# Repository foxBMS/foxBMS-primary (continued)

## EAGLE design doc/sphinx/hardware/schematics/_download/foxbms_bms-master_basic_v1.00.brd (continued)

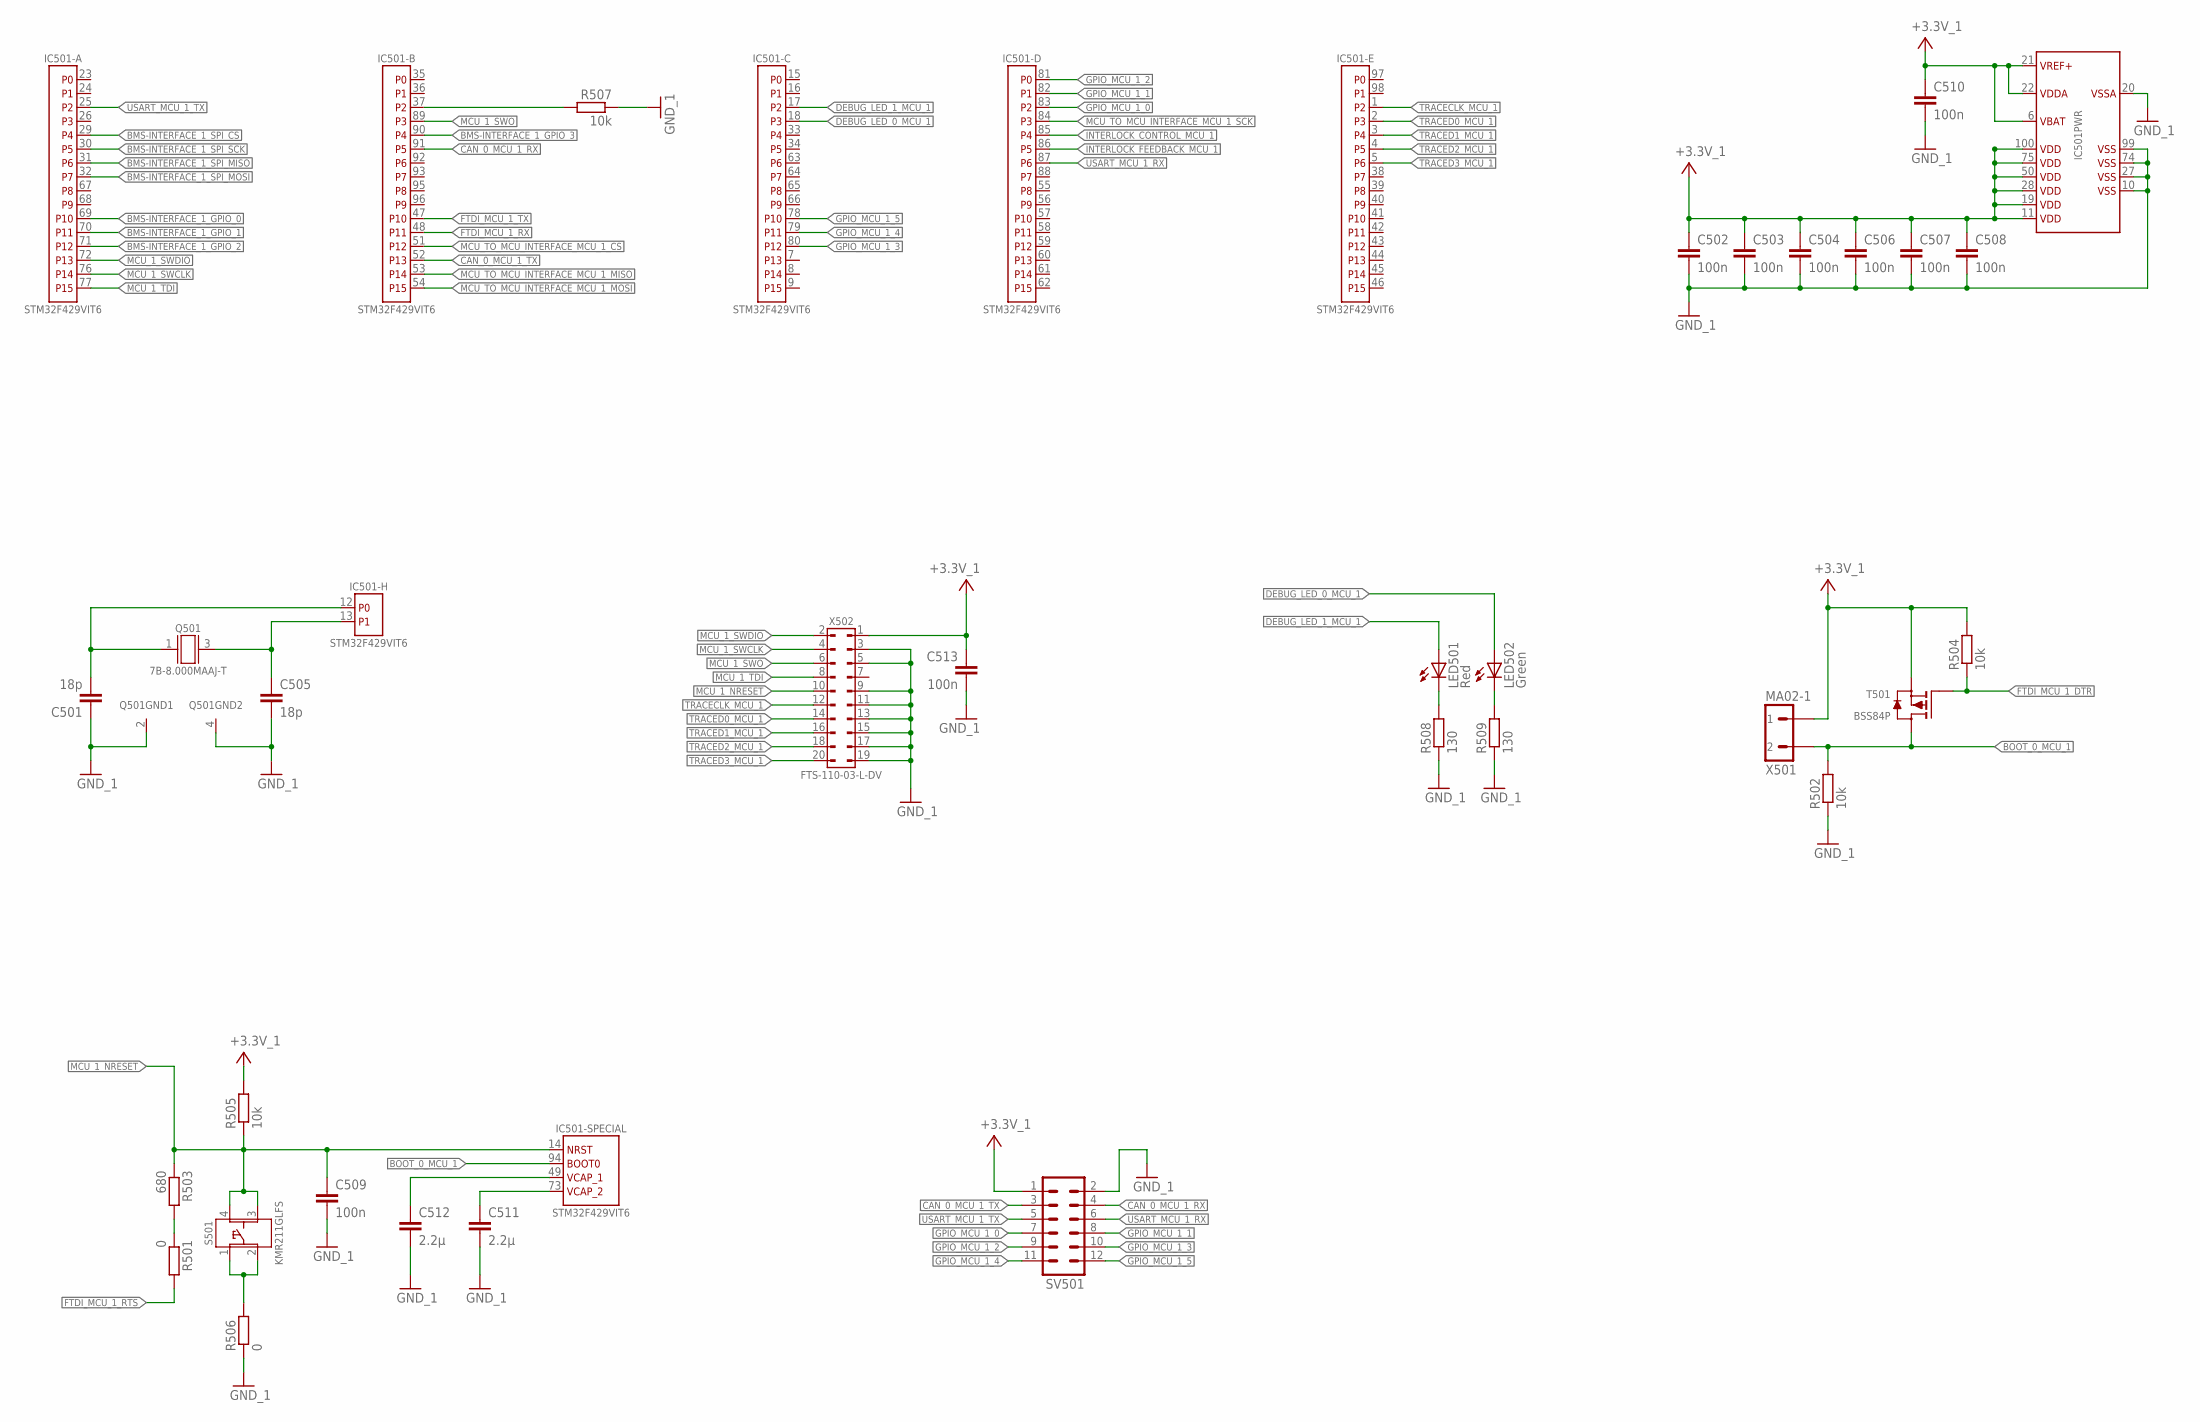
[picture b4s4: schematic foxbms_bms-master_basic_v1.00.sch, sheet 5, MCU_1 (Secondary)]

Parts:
C501, C505: 18p; C0603
C502, C503, C504, C506, C507, C508, C509, C510, C513: 100n; C0603
C511, C512: 2.2µ; C0603
IC501: STM32F429VIT6; IC_SMD_LQFP100_R_ST_REV01
LED501: Red; CHIP-LED0603
LED502: Green; CHIP-LED0603
Q501: 7B-8.000MAAJ-T; G_SMD_5,00MM_X_3,20MM_0,90MM_(7B)_TXC_REV01
R501, R506: 0; R0603
R502, R504, R505, R507: 10k; R0603
R503: 680; R0603
R508, R509: 130; R0603
S501: KMR211GLFS; S_SMD_4,60MMX2,80MMX1,90MM_R_CK-COMPONENTS_REV01
SV501: MA06-2
T501: BSS84P; V_SMD_SOT23_(TO-236AB)_R_INFINEON_REV01
X501: MA02-1
X502: SAMTEC_FTS_20POL_HEADER_VERTIKAL_REV01; X_SMD_FTS_110-03_(20POL)_R_SAMTEC_REV01

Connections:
+3.3V_1: C502.1, C503.1, C504.1, C506.1, C507.1, C508.1, C510.1, C513.1, IC501.6 (VBAT), IC501.11 (VDD1), IC501.19 (VDD2), IC501.21 (VREF+), IC501.22 (VDDA), IC501.28 (VDD3), IC501.50 (VDD4), IC501.75 (VDD5), IC501.100 (VDD6), R504.2, R505.2, SV501.1, T501.2 (S), X501.1, X502.1; also elsewhere on the board
BMS-INTERFACE_1_GPIO_0: IC501.69 (P10); also elsewhere on the board
BMS-INTERFACE_1_GPIO_1: IC501.70 (P11); also elsewhere on the board
BMS-INTERFACE_1_GPIO_2: IC501.71 (P12); also elsewhere on the board
BMS-INTERFACE_1_GPIO_3: IC501.90 (P4); also elsewhere on the board
BMS-INTERFACE_1_SPI_CS: IC501.29 (P4); also elsewhere on the board
BMS-INTERFACE_1_SPI_MISO: IC501.31 (P6); also elsewhere on the board
BMS-INTERFACE_1_SPI_MOSI: IC501.32 (P7); also elsewhere on the board
BMS-INTERFACE_1_SPI_SCK: IC501.30 (P5); also elsewhere on the board
BOOT_0_MCU_1: IC501.94 (BOOT0), R502.2, T501.3 (D), X501.2
CAN_0_MCU_1_RX: IC501.91 (P5), SV501.4
CAN_0_MCU_1_TX: IC501.52 (P13), SV501.3
DEBUG_LED_0_MCU_1: IC501.18 (P3), LED502.A
DEBUG_LED_1_MCU_1: IC501.17 (P2), LED501.A
FTDI_MCU_1_DTR: R504.1, T501.1 (G); also elsewhere on the board
FTDI_MCU_1_RTS: R501.2; also elsewhere on the board
FTDI_MCU_1_RX: IC501.48 (P11); also elsewhere on the board
FTDI_MCU_1_TX: IC501.47 (P10); also elsewhere on the board
GND_1: C501.1, C502.2, C503.2, C504.2, C505.2, C506.2, C507.2, C508.2, C509.2, C510.2, C511.2, C512.2, C513.2, IC501.10 (VSS1), IC501.20 (VSSA), IC501.27 (VSS2), IC501.74 (VSS3), IC501.99 (VSS4), Q501.2 (GND), Q501.4 (GND), R502.1, R506.1, R507.1, R508.1, R509.1, SV501.2, X502.3, X502.5, X502.9, X502.11, X502.13, X502.15, X502.17, X502.19; also elsewhere on the board
GPIO_MCU_1_0: IC501.83 (P2), SV501.7
GPIO_MCU_1_1: IC501.82 (P1), SV501.8
GPIO_MCU_1_2: IC501.81 (P0), SV501.9
GPIO_MCU_1_3: IC501.80 (P12), SV501.10
GPIO_MCU_1_4: IC501.79 (P11), SV501.11
GPIO_MCU_1_5: IC501.78 (P10), SV501.12
INTERLOCK_CONTROL_MCU_1: IC501.85 (P4); also elsewhere on the board
INTERLOCK_FEEDBACK_MCU_1: IC501.86 (P5); also elsewhere on the board
MCU_1_NRESET: C509.1, IC501.14 (NRST), R503.1, R505.1, S501.3, S501.4, X502.10
MCU_1_SWCLK: IC501.76 (P14), X502.4
MCU_1_SWDIO: IC501.72 (P13), X502.2
MCU_1_SWO: IC501.89 (P3), X502.6
MCU_1_TDI: IC501.77 (P15), X502.8
MCU_TO_MCU_INTERFACE_MCU_1_CS: IC501.51 (P12); also elsewhere on the board
MCU_TO_MCU_INTERFACE_MCU_1_MISO: IC501.53 (P14); also elsewhere on the board
MCU_TO_MCU_INTERFACE_MCU_1_MOSI: IC501.54 (P15); also elsewhere on the board
MCU_TO_MCU_INTERFACE_MCU_1_SCK: IC501.84 (P3); also elsewhere on the board
unnamed: C501.2, IC501.12 (P0), Q501.1 (A)
unnamed: C505.1, IC501.13 (P1), Q501.3 (B)
unnamed: R506.2, S501.1, S501.2
unnamed: LED502.C, R509.2
unnamed: LED501.C, R508.2
unnamed: C511.1, IC501.73 (VCAP_2)
unnamed: C512.1, IC501.49 (VCAP_1)
unnamed: IC501.37 (P2), R507.2
unnamed: R501.1, R503.2
TRACECLK_MCU_1: IC501.1 (P2), X502.12
TRACED0_MCU_1: IC501.2 (P3), X502.14
TRACED1_MCU_1: IC501.3 (P4), X502.16
TRACED2_MCU_1: IC501.4 (P5), X502.18
TRACED3_MCU_1: IC501.5 (P6), X502.20
USART_MCU_1_RX: IC501.87 (P6), SV501.6
USART_MCU_1_TX: IC501.25 (P2), SV501.5

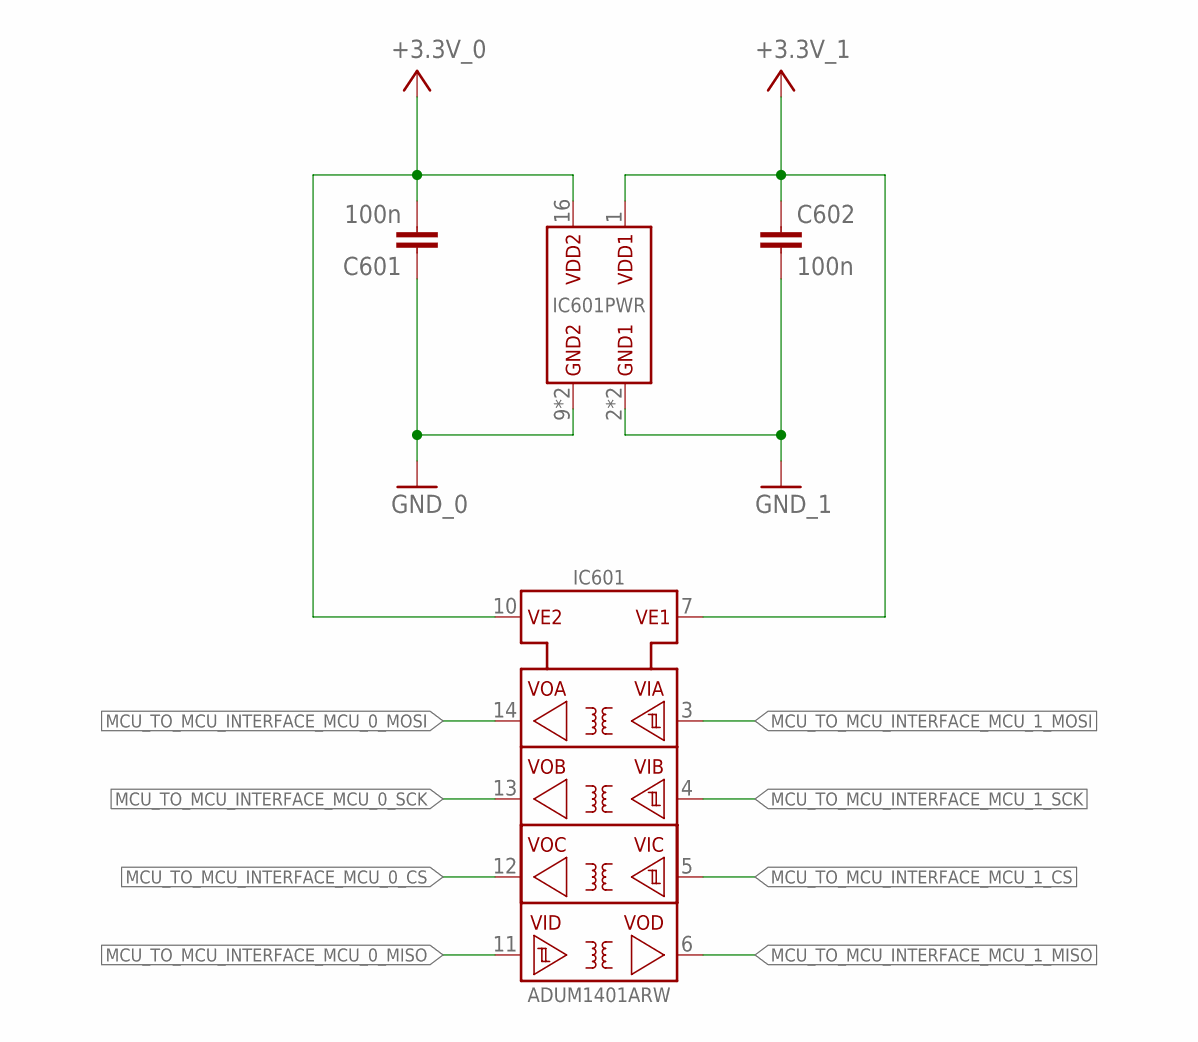
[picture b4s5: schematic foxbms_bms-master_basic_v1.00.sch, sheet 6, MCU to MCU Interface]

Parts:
C601, C602: 100n; C0603
IC601: ADUM1401ARW; IC_SMD_SOIC-16_(JEDEC_MS-013-AA)_R_ANALOG_REV01

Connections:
+3.3V_0: C601.2, IC601.10 (VE2), IC601.16 (VDD2); also elsewhere on the board
+3.3V_1: C602.1, IC601.1 (VDD1), IC601.7 (VE1); also elsewhere on the board
GND_0: C601.1, IC601.9 (GND2), IC601.15 (GND2); also elsewhere on the board
GND_1: C602.2, IC601.2 (GND1), IC601.8 (GND1); also elsewhere on the board
MCU_TO_MCU_INTERFACE_MCU_0_CS: IC601.12 (VOC); also elsewhere on the board
MCU_TO_MCU_INTERFACE_MCU_0_MISO: IC601.11 (VID); also elsewhere on the board
MCU_TO_MCU_INTERFACE_MCU_0_MOSI: IC601.14 (VOA); also elsewhere on the board
MCU_TO_MCU_INTERFACE_MCU_0_SCK: IC601.13 (VOB); also elsewhere on the board
MCU_TO_MCU_INTERFACE_MCU_1_CS: IC601.5 (VIC); also elsewhere on the board
MCU_TO_MCU_INTERFACE_MCU_1_MISO: IC601.6 (VOD); also elsewhere on the board
MCU_TO_MCU_INTERFACE_MCU_1_MOSI: IC601.3 (VIA); also elsewhere on the board
MCU_TO_MCU_INTERFACE_MCU_1_SCK: IC601.4 (VIB); also elsewhere on the board

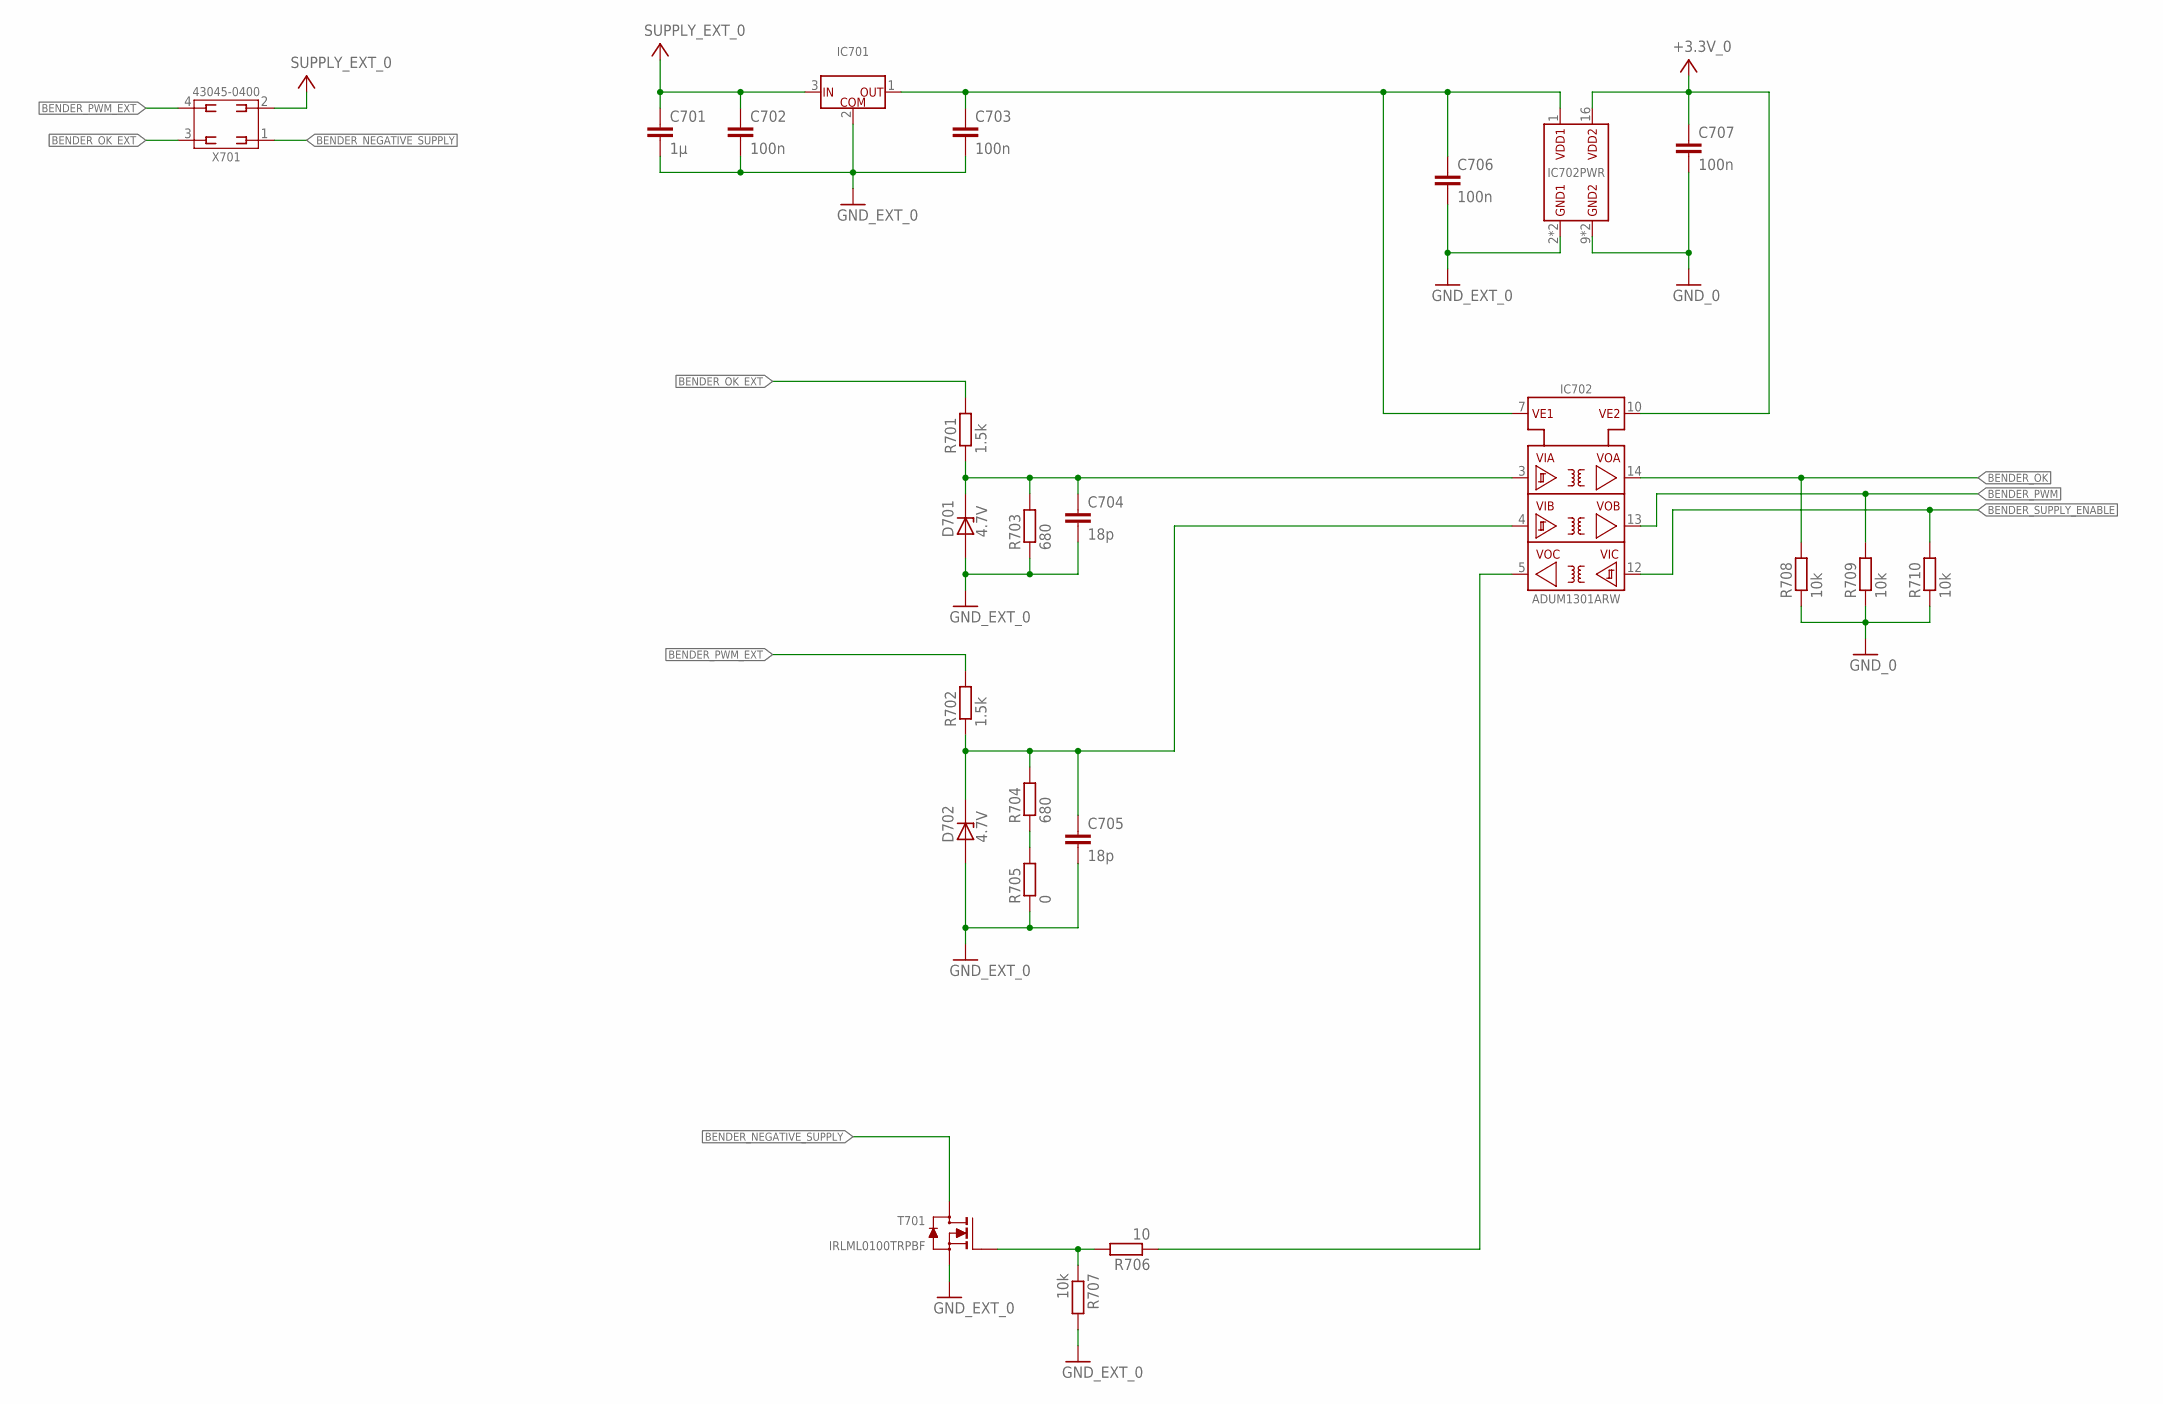
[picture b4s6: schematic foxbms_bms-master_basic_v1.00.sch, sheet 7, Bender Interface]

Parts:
C701: 1µ; C0603
C702, C703, C706, C707: 100n; C0603
C704, C705: 18p; C0603
D701, D702: 4.7V; SOD323
IC701: UA78L05ACPK; IC_SMD_SOT-89_(SC-62/TO-243)_(R-PSSO-F3)_R_TI_REV01
IC702: ADUM1301ARW; IC_SMD_SOIC-16_(JEDEC_MS-013-AA)_R_ANALOG_REV01
R701, R702: 1.5k; R0603
R703, R704: 680; R0603
R705: 0; R0603
R706: 10; R0603
R707, R708, R709, R710: 10k; R0603
T701: IRLML0100TRPBF; V_SMD_SOT-23_(TO-236AB)_R_IR_REV01
X701: 43045-0400_MOLEX_4PIN; X_TH_MOLEX_43045-0400_R_REV01

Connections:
+3.3V_0: C707.1, IC702.10 (VE2), IC702.16 (VDD2); also elsewhere on the board
BENDER_ADUM_SUPPLY: C703.1, C706.1, IC701.1 (OUT), IC702.1 (VDD1), IC702.7 (VE1)
BENDER_NEGATIVE_SUPPLY: T701.3 (D), X701.1
BENDER_OK: IC702.14 (VOA), R708.2; also elsewhere on the board
BENDER_OK_EXT: R701.2, X701.3
BENDER_PWM: IC702.13 (VOB), R709.2; also elsewhere on the board
BENDER_PWM_EXT: R702.2, X701.4
BENDER_SUPPLY_ENABLE: IC702.12 (VIC), R710.2; also elsewhere on the board
GND_0: C707.2, IC702.9 (GND2), IC702.15 (GND2), R708.1, R709.1, R710.1; also elsewhere on the board
GND_EXT_0: C701.2, C702.2, C703.2, C704.2, C705.2, C706.2, D701.A, D702.A, IC701.2 (COM), IC702.2 (GND1), IC702.8 (GND1), R703.1, R705.1, R707.2, T701.2 (S); also elsewhere on the board
unnamed: IC702.5 (VOC), R706.1
unnamed: R706.2, R707.1, T701.1 (G)
unnamed: C705.1, D702.C (K), IC702.4 (VIB), R702.1, R704.2
unnamed: C704.1, D701.C (K), IC702.3 (VIA), R701.1, R703.2
unnamed: R704.1, R705.2
SUPPLY_EXT_0: C701.1, C702.1, IC701.3 (IN), X701.2; also elsewhere on the board

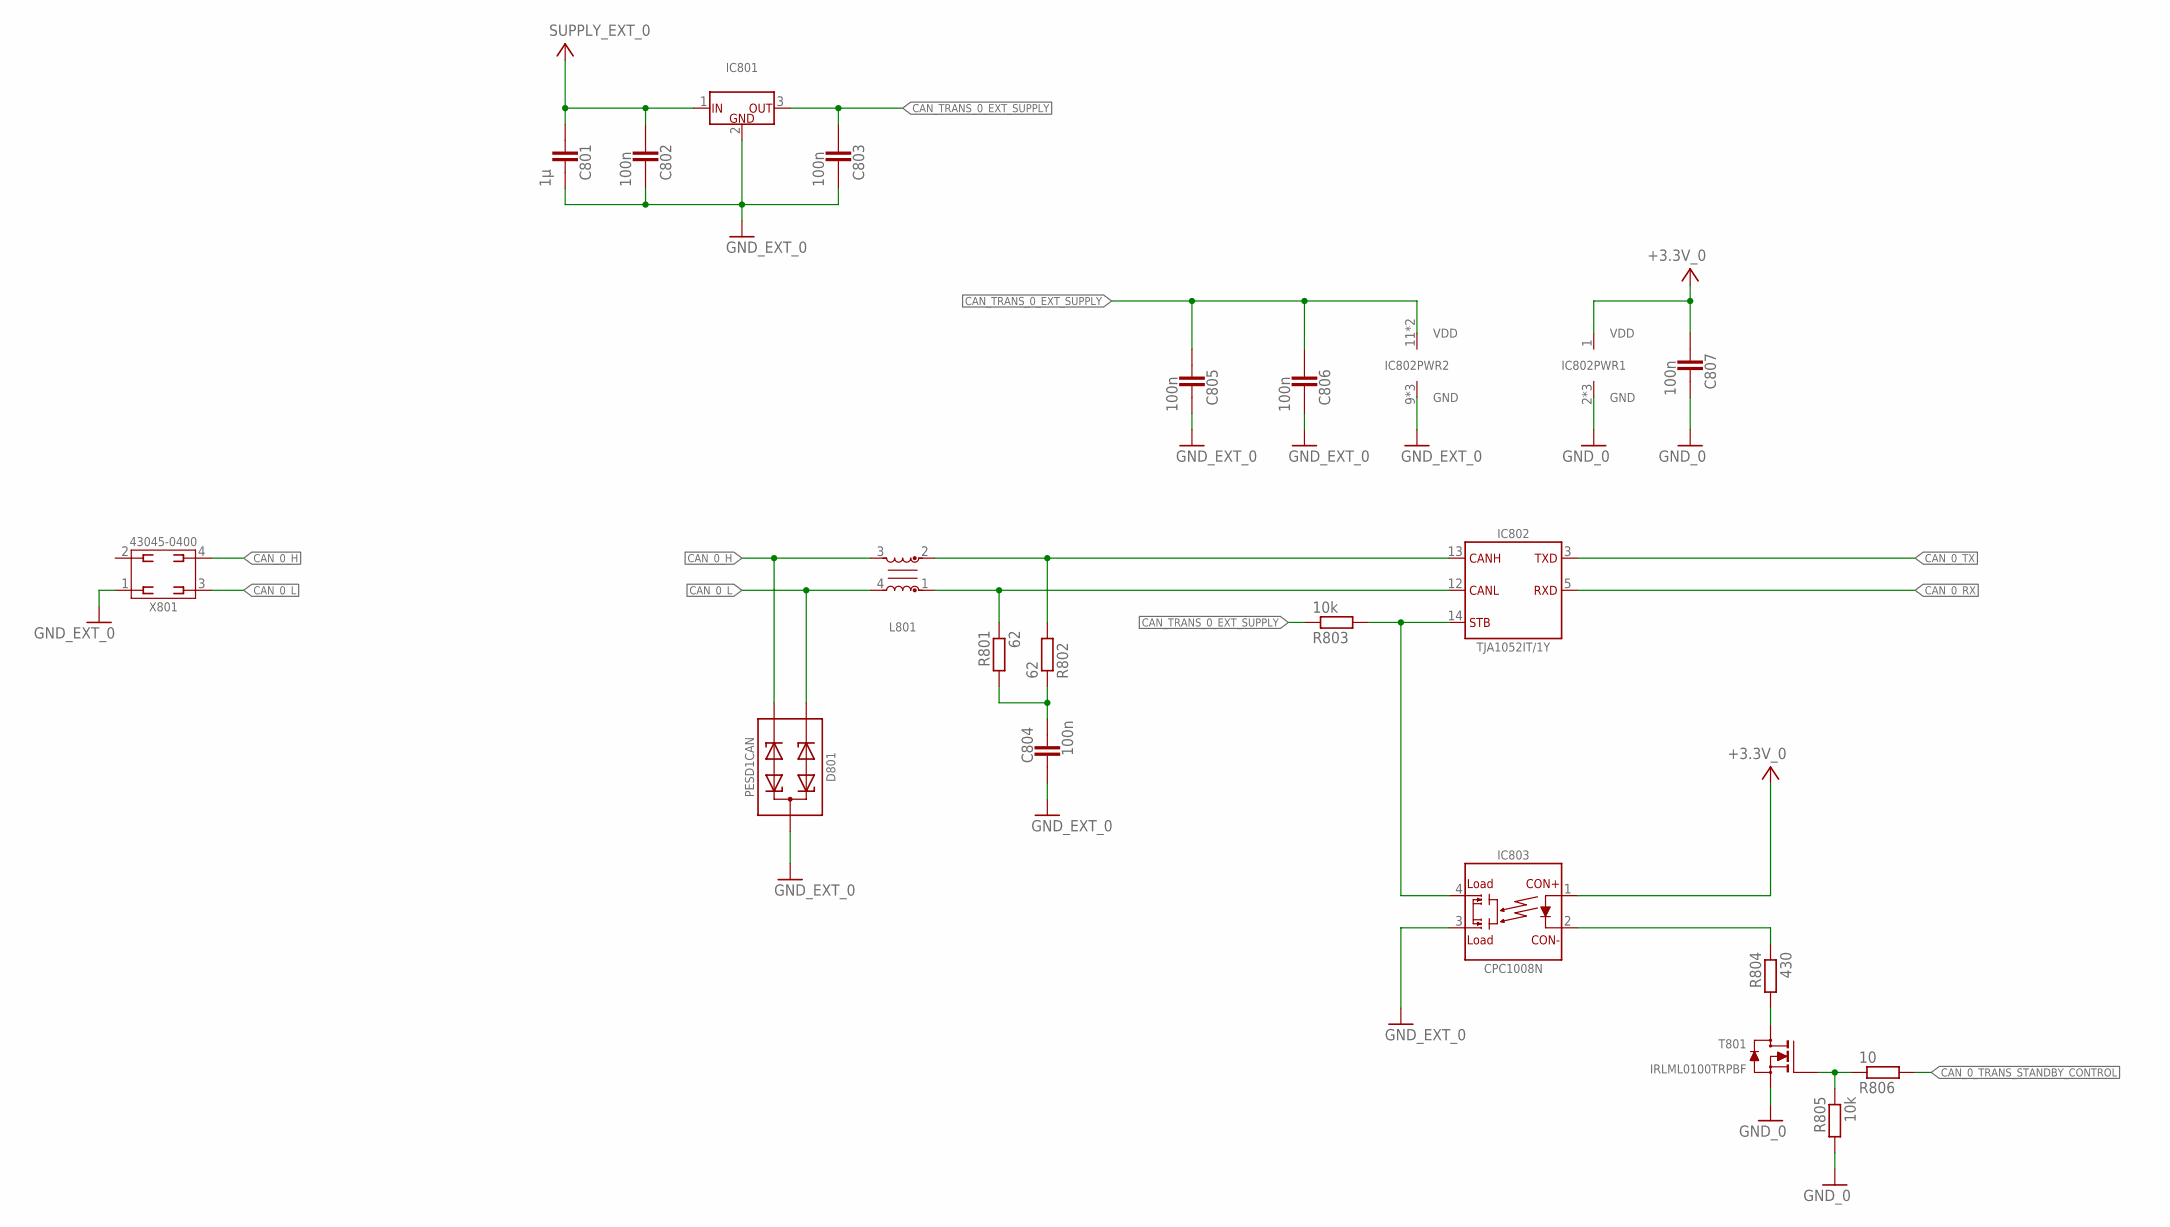
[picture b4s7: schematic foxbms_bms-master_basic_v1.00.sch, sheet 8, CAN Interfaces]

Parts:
C801: 1µ; 0603
C802, C803, C804, C805, C806, C807: 100n; 0603
D801: PESD1CAN; D_SMD_SOT23_(TO-236AB)_R_NXP_REV01
IC801: KA7805ERTF; IC_SMD_TO-252_(D-PAK)_R_FAIRCHILD_REV01
IC802: TJA1052IT/1Y; IC_SMD_SO16_(SOT162-1)_R_NXP_REV01
IC803: CPC1008N; K_SMD_SOP-4_R_IXYS_REV01
L801: B82789C0513H001; L_SMD_FILTER_HF_R_EPCOS_SIMDAD_1812_REV01
R801, R802: 62; 0603
R803, R805: 10k; 0603
R804: 430; 0603
R806: 10; 0603
T801: IRLML0100TRPBF; V_SMD_SOT-23_(TO-236AB)_R_IR_REV01
X801: 43045-0400_MOLEX_4PIN; X_TH_MOLEX_43045-0400_R_REV01

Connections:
+3.3V_0: C807.2, IC802.1 (VDD), IC803.1 (CON+); also elsewhere on the board
CAN_0_H: D801.2, L801.3, X801.4
CAN_0_L: D801.1, L801.4, X801.3
CAN_0_RX: IC802.5 (RXD); also elsewhere on the board
CAN_0_TRANS_STANDBY_CONTROL: R806.2; also elsewhere on the board
CAN_0_TX: IC802.3 (TXD); also elsewhere on the board
CAN_L_INT: IC802.12 (CANL), L801.1, R801.1
CAN_SPLIT: C804.1, R801.2, R802.1
CAN_TRANS_0_EXT_SUPPLY: C803.2, C805.2, C806.2, IC801.3 (OUT), IC802.11 (VDD), IC802.16 (VDD), R803.1
CAN_TRANS_0_STANDBY: IC802.14 (STB), IC803.4, R803.2
GND_0: C807.1, IC802.2 (GND), IC802.7 (GND), IC802.8 (GND), R805.2, T801.2 (S); also elsewhere on the board
GND_EXT_0: C801.1, C802.1, C803.1, C804.2, C805.1, C806.1, D801.3, IC801.2 (GND), IC802.9 (GND), IC802.10 (GND), IC802.15 (GND), IC803.3, X801.1; also elsewhere on the board
unnamed: R804.2, T801.3 (D)
unnamed: IC802.13 (CANH), L801.2, R802.2
unnamed: IC803.2 (CON-), R804.1
unnamed: R805.1, R806.1, T801.1 (G)
SUPPLY_EXT_0: C801.2, C802.2, IC801.1 (IN); also elsewhere on the board

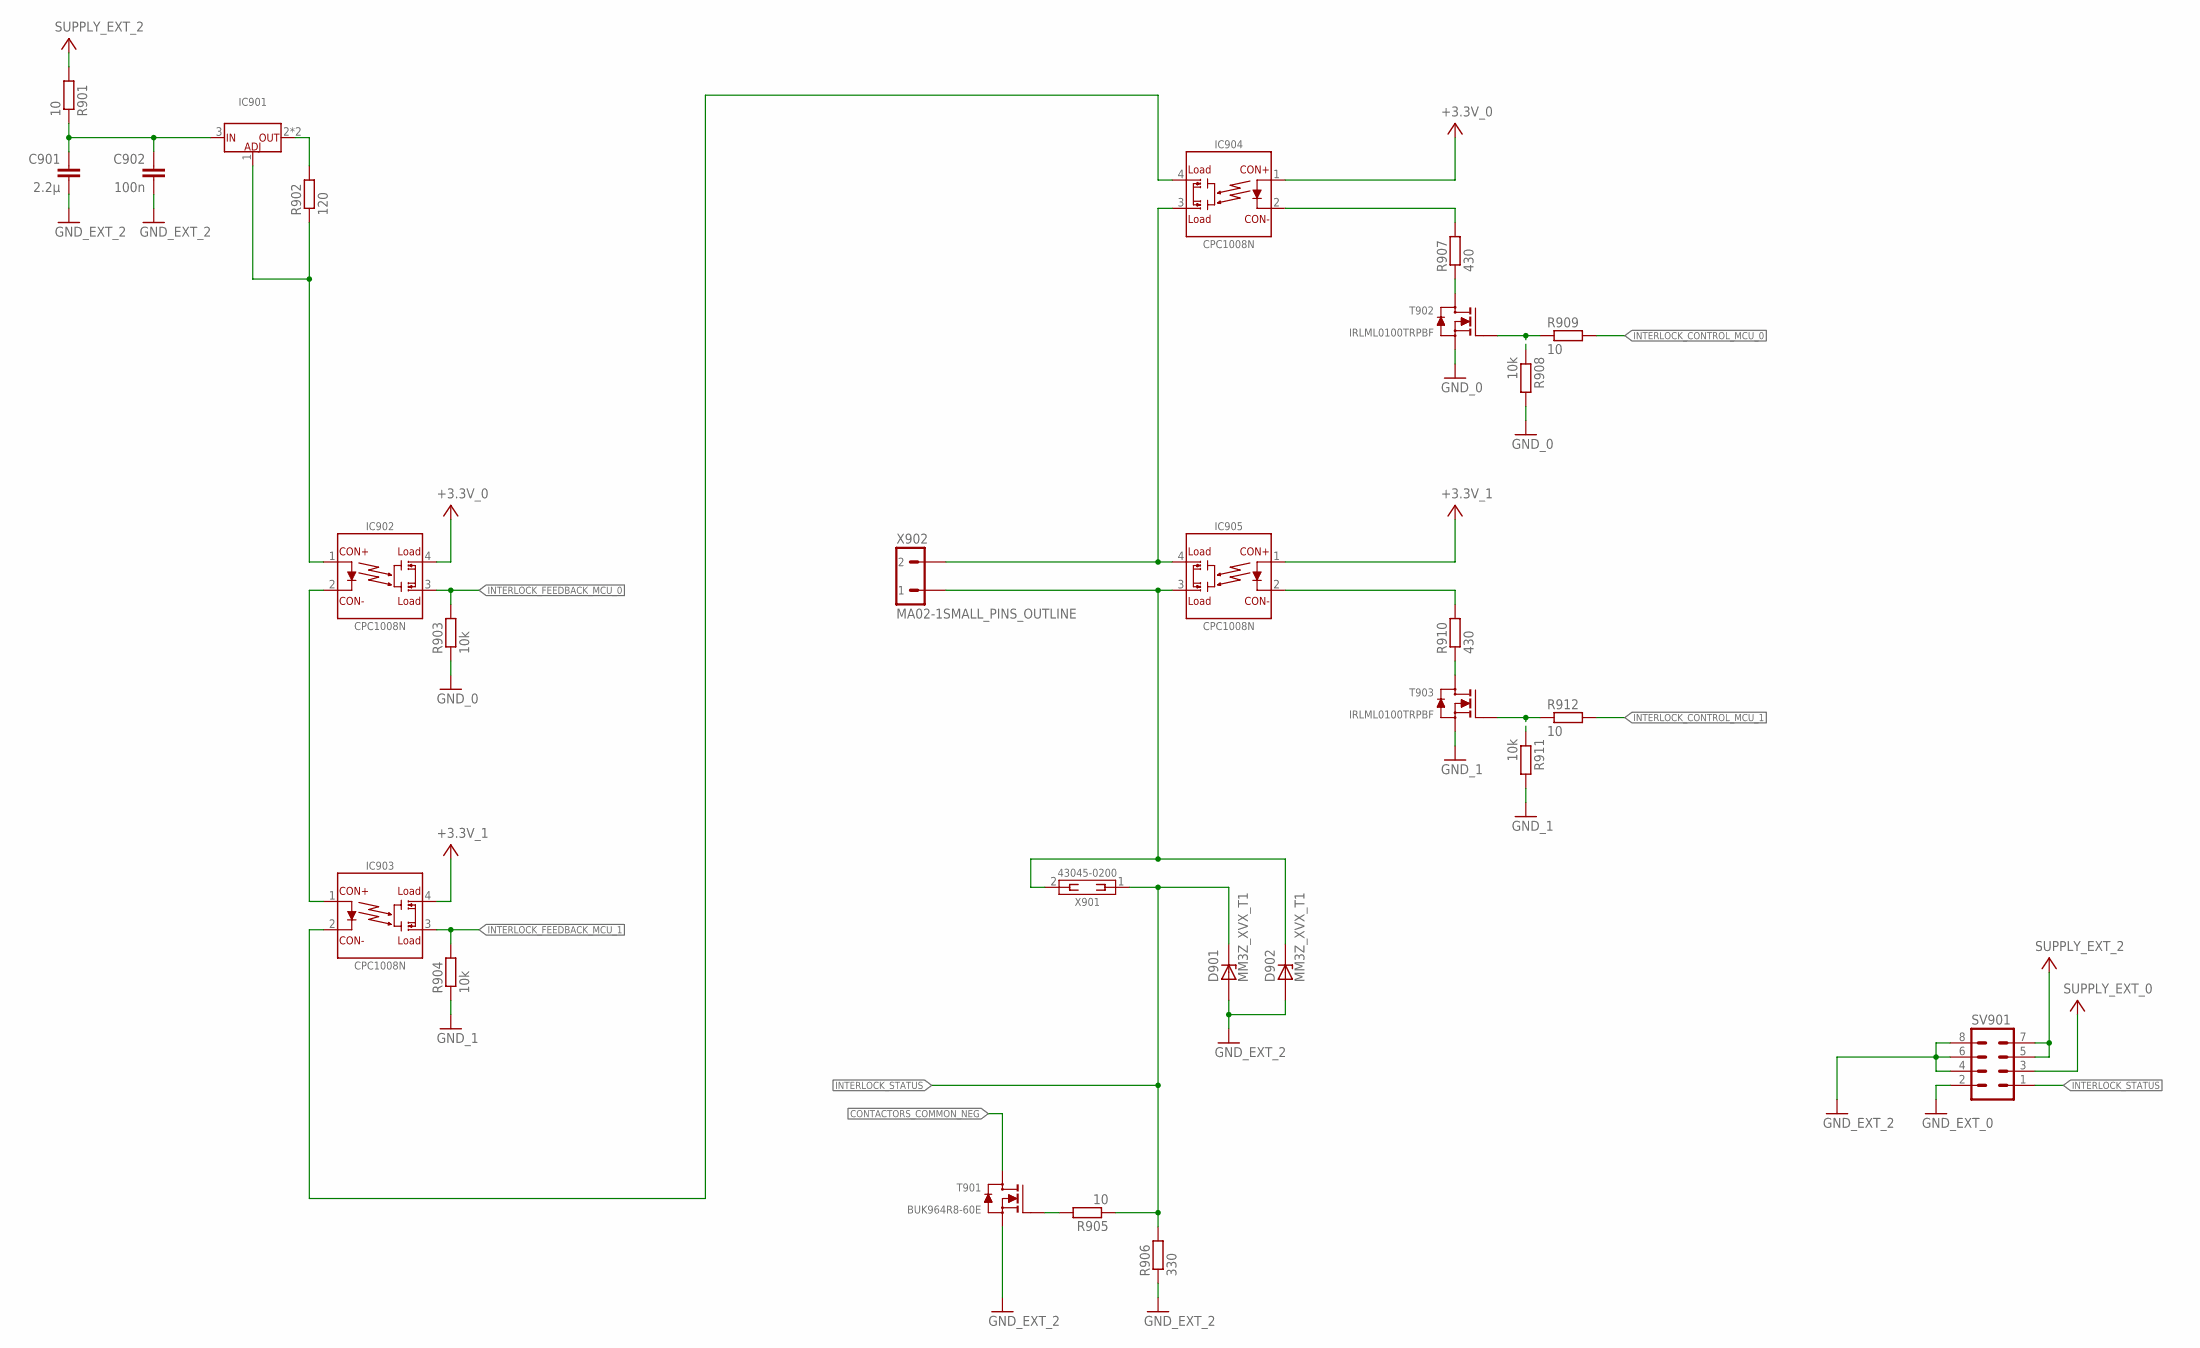
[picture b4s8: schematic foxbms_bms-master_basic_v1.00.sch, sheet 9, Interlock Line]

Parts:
C901: 2.2µ; C0805
C902: 100n; C0603
D901, D902: MM3Z_XVX_T1; SOD323
IC901: LM317MBSTT3G; IC_SMD_SOT-223_(TO-261)_(CASE318E-04)_R_REV01
IC902, IC903, IC904, IC905: CPC1008N; K_SMD_SOP-4_R_IXYS_REV01
R901, R905, R909, R912: 10; R0603
R902: 120; R0603
R903, R904, R908, R911: 10k; R0603
R906: 330; R0603
R907, R910: 430; R0603
SV901: MA04-2
T901: BUK964R8-60E; V_SMD_TO-263_(D²PAK)_R_NXP_REV01
T902, T903: IRLML0100TRPBF; V_SMD_SOT-23_(TO-236AB)_R_IR_REV01
X901: 43045-0200_MOLEX_2PIN; X_TH_MOLEX_43045-0200_R_REV01
X902: MA02-1SMALL_PINS_OUTLINE; MA02-1A

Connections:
+3.3V_0: IC902.4, IC904.1 (CON+); also elsewhere on the board
+3.3V_1: IC903.4, IC905.1 (CON+); also elsewhere on the board
CONTACTORS_COMMON_NEG: T901.2 (D); also elsewhere on the board
GND_0: R903.1, R908.2, T902.2 (S); also elsewhere on the board
GND_1: R904.1, R911.2, T903.2 (S); also elsewhere on the board
GND_EXT_0: SV901.2; also elsewhere on the board
GND_EXT_2: C901.2, C902.2, D901.A, D902.A, R906.1, SV901.4, SV901.6, SV901.8, T901.3 (S); also elsewhere on the board
INTERLOCK_CONTROL_MCU_0: R909.2; also elsewhere on the board
INTERLOCK_CONTROL_MCU_1: R912.2; also elsewhere on the board
INTERLOCK_FEEDBACK_MCU_0: IC902.3, R903.2; also elsewhere on the board
INTERLOCK_FEEDBACK_MCU_1: IC903.3, R904.2; also elsewhere on the board
INTERLOCK_STATUS: D901.C (K), R905.1, R906.2, SV901.1, X901.1
unnamed: R905.2, T901.1 (G)
unnamed: D902.C (K), IC905.3, X901.2, X902.1
unnamed: R907.1, T902.3 (D)
unnamed: R910.1, T903.3 (D)
unnamed: C901.1, C902.1, IC901.3 (IN), R901.1
unnamed: IC901.2 (OUT), IC901.4 (OUT), R902.2
unnamed: IC901.1 (ADJ), IC902.1 (CON+), R902.1
unnamed: IC902.2 (CON-), IC903.1 (CON+)
unnamed: IC905.2 (CON-), R910.2
unnamed: R911.1, R912.1, T903.1 (G)
unnamed: IC903.2 (CON-), IC904.4
unnamed: IC904.2 (CON-), R907.2
unnamed: R908.1, R909.1, T902.1 (G)
unnamed: IC904.3, IC905.4, X902.2
SUPPLY_EXT_0: SV901.3; also elsewhere on the board
SUPPLY_EXT_2: R901.2, SV901.5, SV901.7; also elsewhere on the board

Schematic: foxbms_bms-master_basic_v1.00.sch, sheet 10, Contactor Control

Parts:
D1001, D1002, D1003, D1004, D1005, D1006: GF1; SMA-DO214AC
F1001, F1002, F1003, F1004, F1005, F1006: 630MA_UMT; F_SMD_11,00MMX3,00MMX3,00MM_(UMT)_R_SCHURTER_REV01
IC1001, IC1002, IC1003, IC1004, IC1005, IC1006: AQV252G2S; K_SMD_SOP-6_R_PANASONIC_REV01
R1001, R1002, R1007, R1008, R1013, R1014: 10; R0603
R1003, R1004, R1009, R1010, R1015, R1016: 10k; R0603
R1005, R1006, R1011, R1012, R1017, R1018: 430; R0603
T1001, T1002, T1003, T1004, T1005, T1006: IRLML0100TRPBF; V_SMD_SOT-23_(TO-236AB)_R_IR_REV01

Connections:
+3.3V_0: IC1001.1, IC1002.1, IC1003.1, IC1004.1, IC1005.1, IC1006.1; also elsewhere on the board
CONTACTORS_COMMON_NEG: D1001.A, D1002.A, D1003.A, D1004.A, D1005.A, D1006.A; also elsewhere on the board
CONTACTOR_0_COIL_POS: D1001.K (C), F1001.2; also elsewhere on the board
CONTACTOR_0_CONTROL: R1001.2; also elsewhere on the board
CONTACTOR_1_COIL_POS: D1003.K (C), F1003.2; also elsewhere on the board
CONTACTOR_1_CONTROL: R1007.2; also elsewhere on the board
CONTACTOR_2_COIL_POS: D1005.K (C), F1005.2; also elsewhere on the board
CONTACTOR_2_CONTROL: R1013.2; also elsewhere on the board
CONTACTOR_3_COIL_POS: D1002.K (C), F1002.2; also elsewhere on the board
CONTACTOR_3_CONTROL: R1002.2; also elsewhere on the board
CONTACTOR_4_COIL_POS: D1004.K (C), F1004.2; also elsewhere on the board
CONTACTOR_4_CONTROL: R1008.2; also elsewhere on the board
CONTACTOR_5_COIL_POS: D1006.K (C), F1006.2; also elsewhere on the board
CONTACTOR_5_CONTROL: R1014.2; also elsewhere on the board
GND_0: R1003.1, R1004.1, R1009.1, R1010.1, R1015.1, R1016.1, T1001.2 (S), T1002.2 (S), T1003.2 (S), T1004.2 (S), T1005.2 (S), T1006.2 (S); also elsewhere on the board
unnamed: IC1002.2, R1006.2
unnamed: R1006.1, T1002.3 (D)
unnamed: IC1001.2, R1005.2
unnamed: R1005.1, T1001.3 (D)
unnamed: R1011.1, T1003.3 (D)
unnamed: IC1003.2, R1011.2
unnamed: IC1004.2, R1012.2
unnamed: R1012.1, T1004.3 (D)
unnamed: IC1005.2, R1017.2
unnamed: R1017.1, T1005.3 (D)
unnamed: IC1006.2, R1018.2
unnamed: R1018.1, T1006.3 (D)
unnamed: F1001.1, IC1001.5
unnamed: F1003.1, IC1003.5
unnamed: F1004.1, IC1004.5
unnamed: F1005.1, IC1005.5
unnamed: F1002.1, IC1002.5
unnamed: F1006.1, IC1006.5
unnamed: R1007.1, R1009.2, T1003.1 (G)
unnamed: R1001.1, R1003.2, T1001.1 (G)
unnamed: R1013.1, R1015.2, T1005.1 (G)
unnamed: R1002.1, R1004.2, T1002.1 (G)
unnamed: R1008.1, R1010.2, T1004.1 (G)
unnamed: R1014.1, R1016.2, T1006.1 (G)
SUPPLY_EXT_2: IC1001.4, IC1001.6, IC1002.4, IC1002.6, IC1003.4, IC1003.6, IC1004.4, IC1004.6, IC1005.4, IC1005.6, IC1006.4, IC1006.6; also elsewhere on the board

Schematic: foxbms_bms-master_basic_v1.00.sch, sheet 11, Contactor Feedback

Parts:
C1101: 1µ; C0603
C1102, C1103, C1104, C1105, C1106, C1107: 100n; C0603
D1101, D1102, D1103, D1104, D1105, D1106: CDSOD323-T05; D_SMD_SOD323_(SC-76)_R_BOURNS_REV01
IC1101: UA78L05ACPK; IC_SMD_SOT-89_(SC-62/TO-243)_(R-PSSO-F3)_R_TI_REV01
IC1102, IC1103: ADUM1300ARW; IC_SMD_SOIC-16_(JEDEC_MS-013-AA)_R_ANALOG_REV01
R1101, R1102, R1103, R1104, R1105, R1106: 47; R0603
R1107, R1108, R1109, R1110, R1111, R1112: 10k; R0603

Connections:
+3.3V_0: C1106.1, C1107.1, IC1102.10 (VE2), IC1102.16 (VDD2), IC1103.10 (VE2), IC1103.16 (VDD2); also elsewhere on the board
CONTACTOR_0_FEEDBACK: IC1102.14 (VOA); also elsewhere on the board
CONTACTOR_0_FEEDBACK_EXT: R1101.1; also elsewhere on the board
CONTACTOR_1_FEEDBACK: IC1102.13 (VOB); also elsewhere on the board
CONTACTOR_1_FEEDBACK_EXT: R1102.1; also elsewhere on the board
CONTACTOR_2_FEEDBACK: IC1102.12 (VOC); also elsewhere on the board
CONTACTOR_2_FEEDBACK_EXT: R1103.1; also elsewhere on the board
CONTACTOR_3_FEEDBACK: IC1103.14 (VOA); also elsewhere on the board
CONTACTOR_3_FEEDBACK_EXT: R1104.2; also elsewhere on the board
CONTACTOR_4_FEEDBACK: IC1103.13 (VOB); also elsewhere on the board
CONTACTOR_4_FEEDBACK_EXT: R1105.2; also elsewhere on the board
CONTACTOR_5_FEEDBACK: IC1103.12 (VOC); also elsewhere on the board
CONTACTOR_5_FEEDBACK_EXT: R1106.2; also elsewhere on the board
CONTACTOR_FEEDBACK_SUPPLY_EXT: C1103.1, C1104.1, C1105.1, IC1101.1 (OUT), IC1102.1 (VDD1), IC1103.1 (VDD1), R1107.2, R1108.2, R1109.2, R1110.2, R1111.2, R1112.2
GND_0: C1106.2, C1107.2, IC1102.9 (GND2), IC1102.15 (GND2), IC1103.9 (GND2), IC1103.15 (GND2); also elsewhere on the board
GND_EXT_0: C1101.2, C1102.2, C1103.2, C1104.2, C1105.2, D1101.A, D1102.A, D1103.A, D1104.A, D1105.A, D1106.A, IC1101.2 (COM), IC1102.2 (GND1), IC1102.8 (GND1), IC1103.2 (GND1), IC1103.8 (GND1); also elsewhere on the board
unnamed: D1101.C, IC1102.3 (VIA), R1101.2, R1107.1
unnamed: D1103.C, IC1102.4 (VIB), R1102.2, R1109.1
unnamed: D1105.C, IC1102.5 (VIC), R1103.2, R1111.1
unnamed: D1102.C, IC1103.3 (VIA), R1104.1, R1108.1
unnamed: D1104.C, IC1103.4 (VIB), R1105.1, R1110.1
unnamed: D1106.C, IC1103.5 (VIC), R1106.1, R1112.1
SUPPLY_EXT_0: C1101.1, C1102.1, IC1101.3 (IN); also elsewhere on the board

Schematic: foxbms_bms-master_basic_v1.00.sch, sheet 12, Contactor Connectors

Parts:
X1201, X1202, X1203, X1204, X1205, X1206: 43045-0400_MOLEX_4PIN; X_TH_MOLEX_43045-0400_R_REV01

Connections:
CONTACTORS_COMMON_NEG: X1201.4, X1202.4, X1203.4, X1204.4, X1205.4, X1206.4; also elsewhere on the board
CONTACTOR_0_COIL_POS: X1201.3; also elsewhere on the board
CONTACTOR_0_FEEDBACK_EXT: X1201.2; also elsewhere on the board
CONTACTOR_1_COIL_POS: X1203.3; also elsewhere on the board
CONTACTOR_1_FEEDBACK_EXT: X1203.2; also elsewhere on the board
CONTACTOR_2_COIL_POS: X1205.3; also elsewhere on the board
CONTACTOR_2_FEEDBACK_EXT: X1205.2; also elsewhere on the board
CONTACTOR_3_COIL_POS: X1202.3; also elsewhere on the board
CONTACTOR_3_FEEDBACK_EXT: X1202.2; also elsewhere on the board
CONTACTOR_4_COIL_POS: X1204.3; also elsewhere on the board
CONTACTOR_4_FEEDBACK_EXT: X1204.2; also elsewhere on the board
CONTACTOR_5_COIL_POS: X1206.3; also elsewhere on the board
CONTACTOR_5_FEEDBACK_EXT: X1206.2; also elsewhere on the board
GND_EXT_0: X1201.1, X1202.1, X1203.1, X1204.1, X1205.1, X1206.1; also elsewhere on the board
